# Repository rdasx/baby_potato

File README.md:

baby_potato
===========

Baby Potato, an adorably sized Personal Vaporizer modder's board built around the Potato schematics and the OKR-T6/T10

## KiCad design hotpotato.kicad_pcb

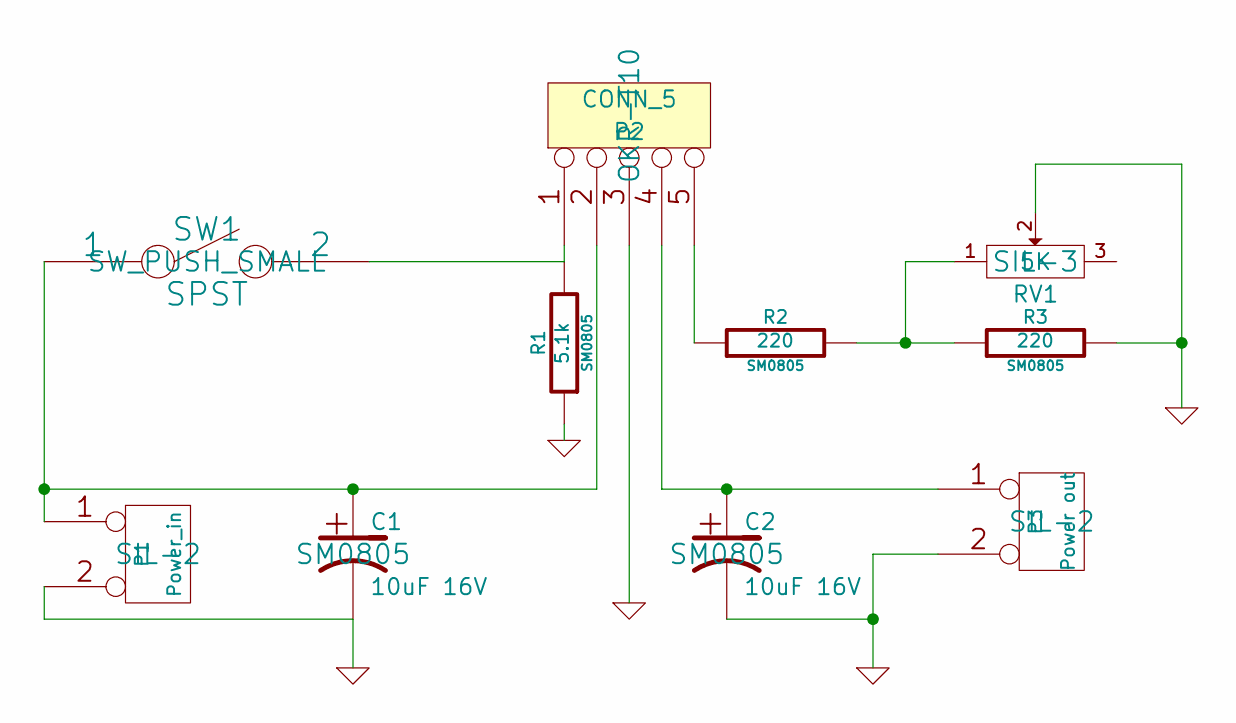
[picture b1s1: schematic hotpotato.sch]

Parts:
C1, C2: 10uF 16V; SM0805
P1: Power_in; SIL-2
P2: CONN_5; OKR-T10
P3: Power out; SIL-2
R1: 5.1k; SM0805
R2, R3: 220; SM0805
RV1: 5K; SIL-3
SW1: SPST; SW_PUSH_SMALL

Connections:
GND: C1.2, C2.2, P1.2 (PM), P2.3, P3.2 (PM), R1.1, R3.2, RV1.2
unnamed: P2.1, R1.2, SW1.2
unnamed: P2.5, R2.1
unnamed: R2.2, R3.1, RV1.1
unnamed: C1.1, P1.1, P2.2, SW1.1
unnamed: C2.1, P2.4, P3.1

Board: 2 copper layers, 10 parts (2 on the bottom side), 6 nets, no tracks yet.

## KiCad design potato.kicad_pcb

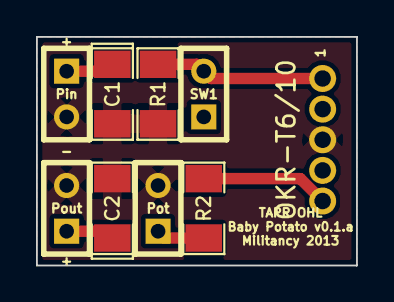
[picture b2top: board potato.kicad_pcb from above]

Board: 2 copper layers, 17.8 x 12.7 mm, 9 parts (0 on the bottom side), 6 nets.

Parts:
C1, C2: 10uF 16V; SM1206POL
P2: OKR-T6/10; OKR-T10
Pin: Power_in; SIL-2
Pot: 200; SIL-2
Pout: Power out; SIL-2
R1: 5.1k; SM1206
R2: 220; SM1206
SW1: SPST; SIL-2

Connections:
GND: C1.2, C2.2, P2.3, Pin.2, Pot.2, Pout.2, R1.1
unnamed: P2.1, R1.2, SW1.2
unnamed: P2.5, R2.1
unnamed: Pot.1, R2.2
unnamed: C1.1, P2.2, Pin.1, SW1.1
unnamed: C2.1, P2.4, Pout.1

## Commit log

2013-09-08 Initial Release
2013-10-02 wider traces
2013-10-02 cleanup
2013-10-02 v0.1.a render
2014-03-22 BOM added
2014-03-23 added Documentation
2014-03-23 fixing mess
2014-03-23 more mess cleaning
